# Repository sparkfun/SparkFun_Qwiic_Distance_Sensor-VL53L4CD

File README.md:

SparkFun Distance Sensor - VL53L4CD (Qwiic)
========================================

[*SparkFun Distance Sensor - VL53L4CD (Qwiic) (SEN-18993)*](https://www.sparkfun.com/products/18993)

This SparkFun Distance Sensor Breakout utilizes the VL53L4CD next generation ToF (Time of Flight) sensor module to give you the highly accurate measurements at short ranges for its size. The VL53L4CD from STMicroelectronics uses a VCSEL (Vertical Cavity Surface Emitting Laser) to emit an infrared laser to time the reflection to the target. That means that you will be able to measure the distance to an object from 1mm to 1300mm away with millimeter resolution! To make it even easier to get your readings, all communication is enacted exclusively via I<sup>2</sup>C, utilizing our handy Qwiic system so no soldering is required to connect it to the rest of your system. However, we still have broken out 0.1”-spaced pins in case you prefer to use a breadboard.

Each VL53L4CD sensor features a precision to be 1mm with an accuracy around +/-7mm (white target: 88%, indoor, no infrared) and a minimum read distance of this sensor is 1mm. The field of view for this little breakout has a typical full field of view of 18° with a read rate of up to 100Hz. Make sure to power this board appropriately since it will need 2.6V-3.5V to operate. Lastly, please be sure to remove the protective sticker on the VL53L1X before use otherwise it will, most assuredly, throw off your readings.

**Note:** This is a [CLASS 1](http://en.wikipedia.org/wiki/Laser_safety#Class_1) LASER PRODUCT CLASSIFIED IEC 60825-1 2014.

Repository Contents
-------------------

* **/Hardware** - Eagle design files (.brd, .sch)
* **/Production** - Production panel files (.brd)

Documentation
--------------
* **[Arduino Library](https://github.com/sparkfun/SparkFun_VL53L1X_Arduino_Library)** -  Arduino library for the VL53L1X and VL53L4CD.
* **[VL53L1X Python Package](https://github.com/sparkfun/Qwiic_VL53L1X_Py)** - Python package for the VL53L1X and VL53L4CD.
  * **[ReadtheDocs Documentation](https://qwiic-vl53l1x-py.readthedocs.io/en/latest/)**
* **[Hookup Guide](https://learn.sparkfun.com/tutorials/qwiic-distance-sensor-vl53l1x-vl53l4cd-hookup-guide)** - Basic hookup guide for the VL53L1X and VL53L4CD.

Product Versions
----------------
* [SEN-18993](https://www.sparkfun.com/products/18993) - Initial Release

Version History
---------------
* v1.0 - Initial Release 

License Information
-------------------

This product is _**open source**_! 

Please review the LICENSE.md file for license information. 

If you have any questions or concerns on licensing, please contact technical support on our [SparkFun forums](https://forum.sparkfun.com/viewforum.php?f=152).

Distributed as-is; no warranty is given.

- Your friends at SparkFun.

_<COLLABORATION CREDIT>_

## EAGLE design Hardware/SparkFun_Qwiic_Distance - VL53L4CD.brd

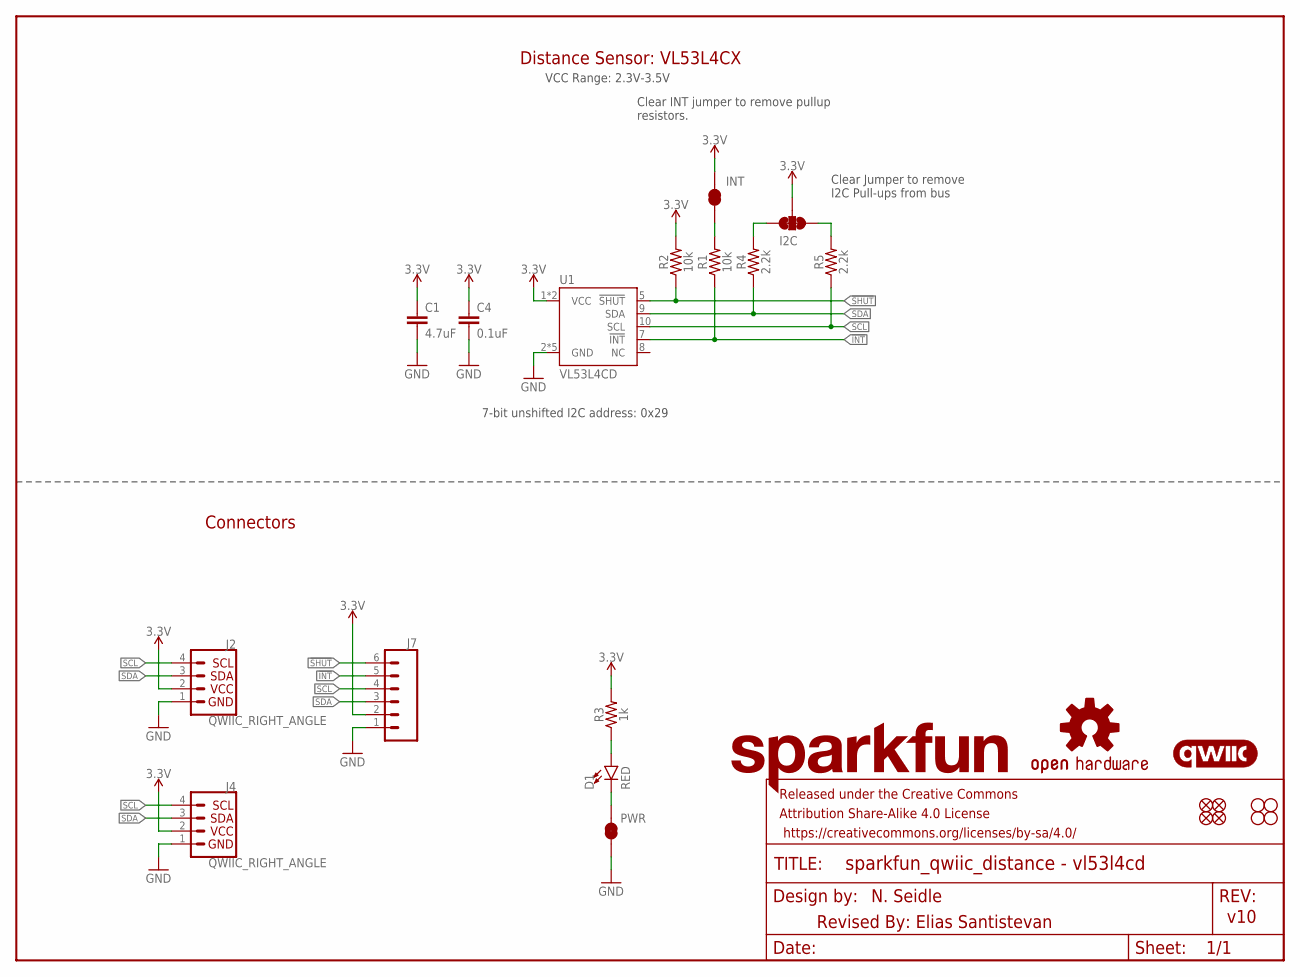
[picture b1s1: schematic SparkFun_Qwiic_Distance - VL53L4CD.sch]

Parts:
C1: 4.7uF; 0603
C4: 0.1uF; 0603
D1: RED; LED-0603
FRAME1: FRAME-LETTER; CREATIVE_COMMONS
I2C: JUMPER-SMT_3_2-NC_TRACE_SILK; SMT-JUMPER_3_2-NC_TRACE_SILK
J2, J4: QWIIC_RIGHT_ANGLE; JST04_1MM_RA
J7: CONN_06NO_SILK_NO_POP; 1X06_NO_SILK
JP1, JP2, JP5, JP6: FIDUCIALUFIDUCIAL; MICRO-FIDUCIAL
JP3, JP4, JP7, JP8: STAND-OFF
JP9: INT; SMT-JUMPER_2_NC_TRACE_SILK
LOGO1: OSHW-LOGOMINI; OSHW-LOGO-MINI
LOGO2: SFE_LOGO_NAME.1_INCH; SFE_LOGO_NAME_.1
LOGO3: QWIIC_LOGO_4MM; QWIIC_4MM
PWR: INT; SMT-JUMPER_2_NC_TRACE_SILK
R1, R2: 10k; 0603
R3: 1k; 0603
R4, R5: 2.2k; 0603
U1: VL53L4CD

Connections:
3.3V: C1.1, C4.1, I2C.2, J2.2, J4.2, J7.2, JP9.2, R2.2, R3.2, U1.1 (VCC), U1.11 (VCC)
!INT: J7.5, R1.1, U1.7 (!INT)
!SHUT: J7.6, R2.1, U1.5 (!SHUT)
GND: C1.2, C4.2, J2.1, J4.1, J7.1, PWR.1, U1.2 (GND), U1.3 (GND), U1.4 (GND), U1.6 (GND), U1.12 (GND)
unnamed: I2C.1, R5.2
unnamed: I2C.3, R4.2
unnamed: D1.A, R3.1
unnamed: JP9.1, R1.2
unnamed: D1.C, PWR.2
SCL: J2.4, J4.4, J7.4, R5.1, U1.10 (SCL)
SDA: J2.3, J4.3, J7.3, R4.1, U1.9 (SDA)

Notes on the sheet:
N. Seidle
v10
7-bit unshifted I2C address: 0x29
Clear Jumper to remove I2C Pull-ups from bus
Clear INT jumper to remove pullup resistors.
Connectors
Distance Sensor: VL53L4CX
VCC Range: 2.3V-3.5V
Revised By: Elias Santistevan

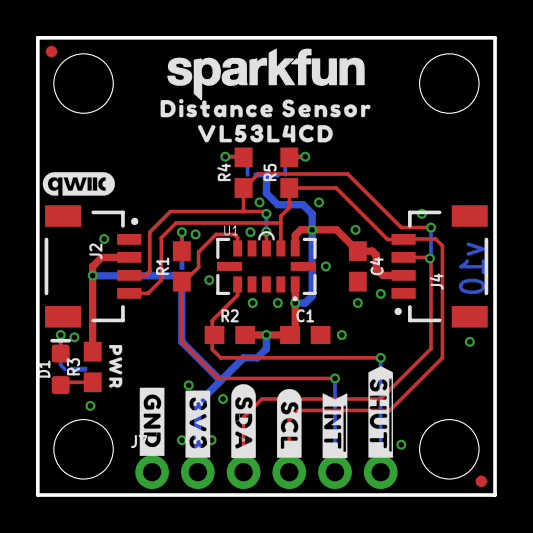
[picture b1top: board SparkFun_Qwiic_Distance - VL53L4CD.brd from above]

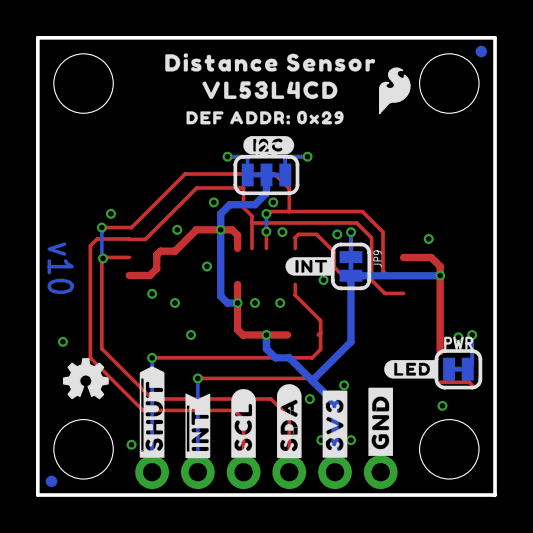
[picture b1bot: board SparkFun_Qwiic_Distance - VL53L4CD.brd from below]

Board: 2 copper layers, 25.4 x 25.4 mm, 50 parts (20 on the bottom side), 11 nets.

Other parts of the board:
U$1, U$12: ##INT##7
U$2, U$13: ##SHUT##6
U$3, U$14: #3V3#1
U$4, U$15: #GND#0
U$5: #I2C#56
U$6, U$16: #SCL#4
U$7, U$17: #SDA#5
U$8, U$18: DISTANCE_SENSOR8
U$9, U$24: VL53L4CD0
U$10: #LED#54
U$11: #INT#55
U$20: DEF_ADDR#54
U$21: 0X2955
U$22: SFE_LOGO_FLAME_.1
U$23: PWR55

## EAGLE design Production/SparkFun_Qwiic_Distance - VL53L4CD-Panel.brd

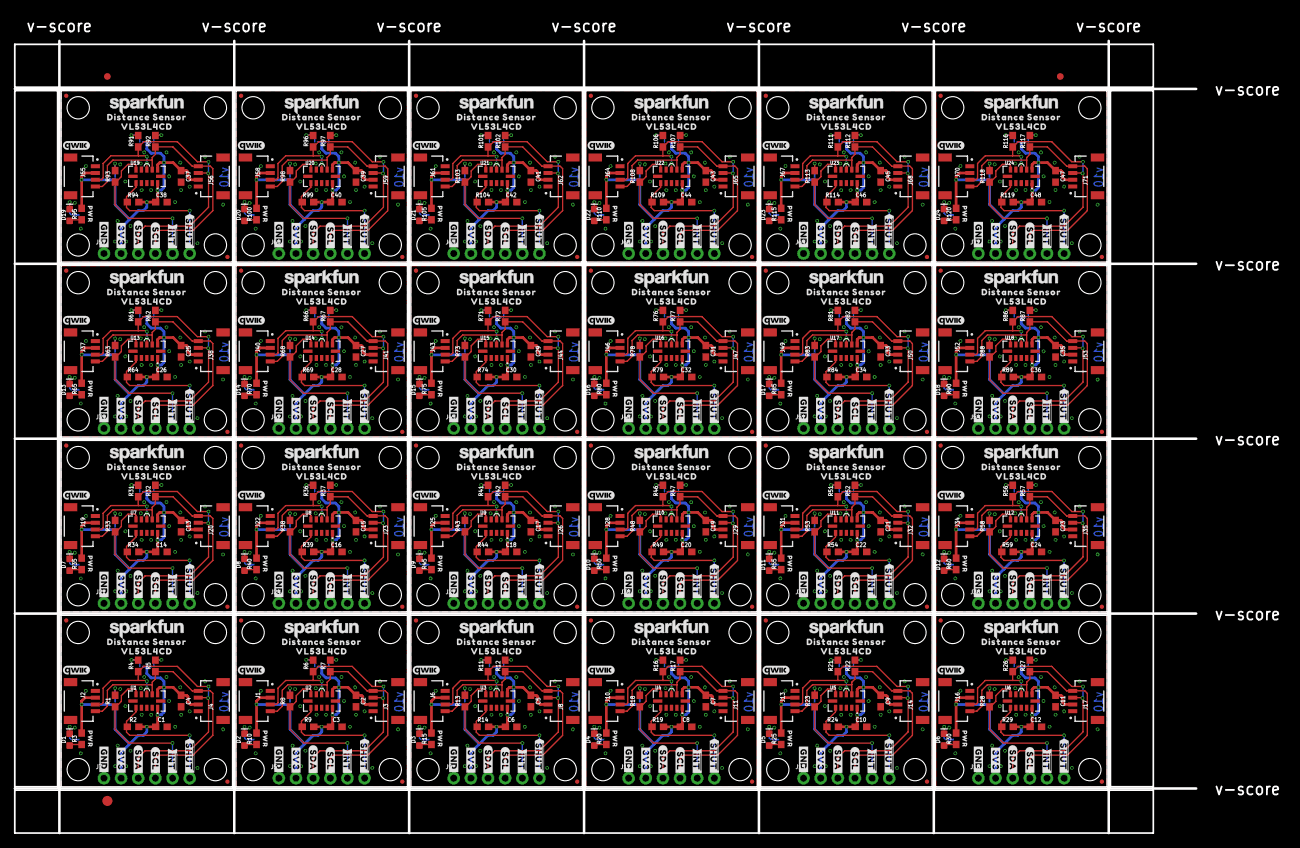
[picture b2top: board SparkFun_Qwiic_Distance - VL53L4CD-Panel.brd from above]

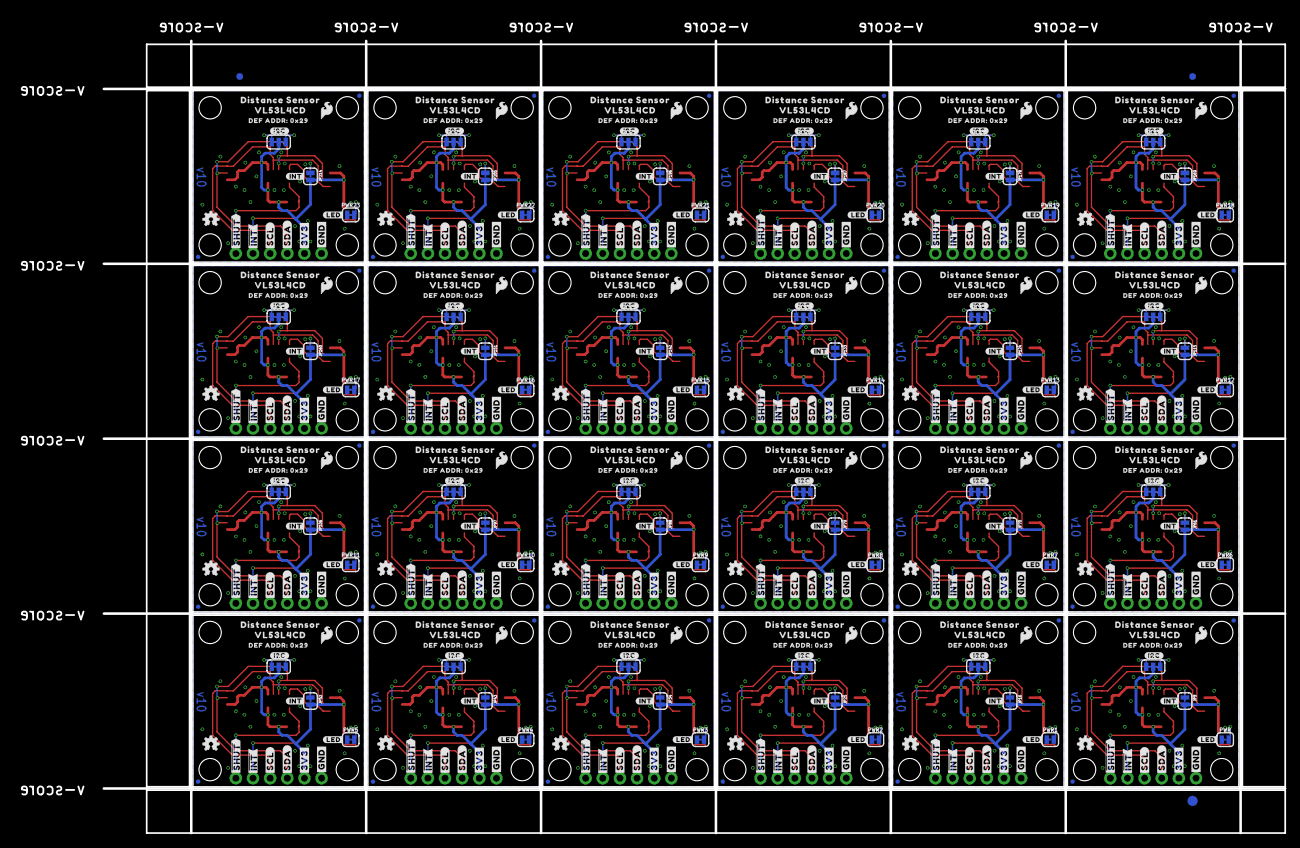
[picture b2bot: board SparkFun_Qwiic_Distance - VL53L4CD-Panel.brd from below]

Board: 2 copper layers, 188.2 x 121.2 mm, 1182 parts (483 on the bottom side), 264 nets.

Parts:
C1, C3, C6, C8, C10, C12, C14, C16, C18, C20, C22, C24, C26, C28, C30, C32, C34, C36, C38, C40, C42, C44, C46, C48: 4.7uF; 0603
C2, C4, C5, C7, C9, C11, C13, C15, C17, C19, C21, C23, C25, C27, C29, C31, C33, C35, C37, C39, C41, C43, C45, C47: 0.1uF; 0603
D1, D2, D3, D4, D5, D6, D7, D8, D9, D10, D11, D12, D13, D14, D15, D16, D17, D18, D19, D20, D21, D22, D23, D24: RED; LED-0603
E$1, E$2, E$3, E$4: FIDUCIAL-1X2
E$5, E$6: FIDUCIAL-1.5X3
I2C, I2C1, I2C2, I2C3, I2C4, I2C5, I2C6, I2C7, I2C8, I2C9, I2C10, I2C11, I2C12, I2C13, I2C14, I2C15, I2C16, I2C17, I2C18, I2C19, I2C20, I2C21, I2C22, I2C23: JUMPER-SMT_3_2-NC_TRACE_SILK; SMT-JUMPER_3_2-NC_TRACE_SILK
J1, J2, J3, J4, J6, J8, J10, J11, J13, J14, J16, J17, J19, J20, J22, J23, J25, J26, J28, J29, J31, J32, J34, J35, J37, J38, J40, J41, J43, J44, J46, J47, J49, J50, J52, J53, J55, J56, J58, J59, J61, J62, J64, J65, J67, J68, J70, J71: QWIIC_RIGHT_ANGLE; JST04_1MM_RA
J5, J7, J9, J12, J15, J18, J21, J24, J27, J30, J33, J36, J39, J42, J45, J48, J51, J54, J57, J60, J63, J66, J69, J72: 1X06_NO_SILK
JP1, JP2, JP5, JP6, JP12, JP13, JP14, JP15, JP21, JP22, JP23, JP24, JP30, JP31, JP32, JP33, JP39, JP40, JP41, JP42, JP48, JP49, JP50, JP51, JP57, JP58, JP59, JP60, JP66, JP67, JP68, JP69, JP75, JP76, JP77, JP78, JP84, JP85, JP86, JP87, JP93, JP94, JP95, JP96, JP102, JP103, JP104, JP105, JP111, JP112, JP113, JP114, JP120, JP121, JP122, JP123, JP129, JP130, JP131, JP132, JP138, JP139, JP140, JP141, JP147, JP148, JP149, JP150, JP156, JP157, JP158, JP159, JP165, JP166, JP167, JP168, JP174, JP175, JP176, JP177, JP183, JP184, JP185, JP186, JP192, JP193, JP194, JP195, JP201, JP202, JP203, JP204, JP210, JP211, JP212, JP213: FIDUCIALUFIDUCIAL; MICRO-FIDUCIAL
JP3, JP4, JP7, JP8, JP10, JP11, JP17, JP18, JP19, JP20, JP26, JP27, JP28, JP29, JP35, JP36, JP37, JP38, JP44, JP45, JP46, JP47, JP53, JP54, JP55, JP56, JP62, JP63, JP64, JP65, JP71, JP72, JP73, JP74, JP80, JP81, JP82, JP83, JP89, JP90, JP91, JP92, JP98, JP99, JP100, JP101, JP107, JP108, JP109, JP110, JP116, JP117, JP118, JP119, JP125, JP126, JP127, JP128, JP134, JP135, JP136, JP137, JP143, JP144, JP145, JP146, JP152, JP153, JP154, JP155, JP161, JP162, JP163, JP164, JP170, JP171, JP172, JP173, JP179, JP180, JP181, JP182, JP188, JP189, JP190, JP191, JP197, JP198, JP199, JP200, JP206, JP207, JP208, JP209, JP215, JP216: STAND-OFF
JP9, JP16, JP25, JP34, JP43, JP52, JP61, JP70, JP79, JP88, JP97, JP106, JP115, JP124, JP133, JP142, JP151, JP160, JP169, JP178, JP187, JP196, JP205, JP214: INT; SMT-JUMPER_2_NC_TRACE_SILK
LOGO1, LOGO4, LOGO7, LOGO10, LOGO13, LOGO16, LOGO19, LOGO22, LOGO25, LOGO28, LOGO31, LOGO34, LOGO37, LOGO40, LOGO43, LOGO46, LOGO49, LOGO52, LOGO55, LOGO58, LOGO61, LOGO64, LOGO67, LOGO70: OSHW-LOGOMINI; OSHW-LOGO-MINI
LOGO2, LOGO5, LOGO8, LOGO11, LOGO14, LOGO17, LOGO20, LOGO23, LOGO26, LOGO29, LOGO32, LOGO35, LOGO38, LOGO41, LOGO44, LOGO47, LOGO50, LOGO53, LOGO56, LOGO59, LOGO62, LOGO65, LOGO68, LOGO71: SFE_LOGO_NAME.1_INCH; SFE_LOGO_NAME_.1
LOGO3, LOGO6, LOGO9, LOGO12, LOGO15, LOGO18, LOGO21, LOGO24, LOGO27, LOGO30, LOGO33, LOGO36, LOGO39, LOGO42, LOGO45, LOGO48, LOGO51, LOGO54, LOGO57, LOGO60, LOGO63, LOGO66, LOGO69, LOGO72: QWIIC_LOGO_4MM; QWIIC_4MM
PWR, PWR1, PWR2, PWR3, PWR4, PWR5, PWR6, PWR7, PWR8, PWR9, PWR10, PWR11, PWR12, PWR13, PWR14, PWR15, PWR16, PWR17, PWR18, PWR19, PWR20, PWR21, PWR22, PWR23: INT; SMT-JUMPER_2_NC_TRACE_SILK
R1, R2, R8, R9, R13, R14, R18, R19, R23, R24, R28, R29, R33, R34, R38, R39, R43, R44, R48, R49, R53, R54, R58, R59, R63, R64, R68, R69, R73, R74, R78, R79, R83, R84, R88, R89, R93, R94, R98, R99, R103, R104, R108, R109, R113, R114, R118, R119: 10k; 0603
R3, R10, R15, R20, R25, R30, R35, R40, R45, R50, R55, R60, R65, R70, R75, R80, R85, R90, R95, R100, R105, R110, R115, R120: 1k; 0603
R4, R5, R6, R7, R11, R12, R16, R17, R21, R22, R26, R27, R31, R32, R36, R37, R41, R42, R46, R47, R51, R52, R56, R57, R61, R62, R66, R67, R71, R72, R76, R77, R81, R82, R86, R87, R91, R92, R96, R97, R101, R102, R106, R107, R111, R112, R116, R117: 2.2k; 0603
U1, U2, U3, U4, U5, U6, U7, U8, U9, U10, U11, U12, U13, U14, U15, U16, U17, U18, U19, U20, U21, U22, U23, U24: VL53L4CX
U$1, U$12, U$19, U$34, U$47, U$57, U$70, U$80, U$93, U$103, U$116, U$126, U$139, U$149, U$162, U$172, U$185, U$195, U$208, U$218, U$231, U$241, U$254, U$264, U$277, U$287, U$300, U$310, U$323, U$333, U$346, U$356, U$369, U$379, U$392, U$402, U$415, U$425, U$438, U$448, U$461, U$471, U$484, U$494, U$507, U$517, U$530, U$540: ##INT##7
U$2, U$13, U$25, U$35, U$48, U$58, U$71, U$81, U$94, U$104, U$117, U$127, U$140, U$150, U$163, U$173, U$186, U$196, U$209, U$219, U$232, U$242, U$255, U$265, U$278, U$288, U$301, U$311, U$324, U$334, U$347, U$357, U$370, U$380, U$393, U$403, U$416, U$426, U$439, U$449, U$462, U$472, U$485, U$495, U$508, U$518, U$531, U$541: ##SHUT##6
U$3, U$14, U$26, U$36, U$49, U$59, U$72, U$82, U$95, U$105, U$118, U$128, U$141, U$151, U$164, U$174, U$187, U$197, U$210, U$220, U$233, U$243, U$256, U$266, U$279, U$289, U$302, U$312, U$325, U$335, U$348, U$358, U$371, U$381, U$394, U$404, U$417, U$427, U$440, U$450, U$463, U$473, U$486, U$496, U$509, U$519, U$532, U$542: #3V3#1
U$4, U$15, U$27, U$37, U$50, U$60, U$73, U$83, U$96, U$106, U$119, U$129, U$142, U$152, U$165, U$175, U$188, U$198, U$211, U$221, U$234, U$244, U$257, U$267, U$280, U$290, U$303, U$313, U$326, U$336, U$349, U$359, U$372, U$382, U$395, U$405, U$418, U$428, U$441, U$451, U$464, U$474, U$487, U$497, U$510, U$520, U$533, U$543: #GND#0
U$5, U$28, U$51, U$74, U$97, U$120, U$143, U$166, U$189, U$212, U$235, U$258, U$281, U$304, U$327, U$350, U$373, U$396, U$419, U$442, U$465, U$488, U$511, U$534: #I2C#56
U$6, U$16, U$29, U$38, U$52, U$61, U$75, U$84, U$98, U$107, U$121, U$130, U$144, U$153, U$167, U$176, U$190, U$199, U$213, U$222, U$236, U$245, U$259, U$268, U$282, U$291, U$305, U$314, U$328, U$337, U$351, U$360, U$374, U$383, U$397, U$406, U$420, U$429, U$443, U$452, U$466, U$475, U$489, U$498, U$512, U$521, U$535, U$544: #SCL#4
U$7, U$17, U$30, U$39, U$53, U$62, U$76, U$85, U$99, U$108, U$122, U$131, U$145, U$154, U$168, U$177, U$191, U$200, U$214, U$223, U$237, U$246, U$260, U$269, U$283, U$292, U$306, U$315, U$329, U$338, U$352, U$361, U$375, U$384, U$398, U$407, U$421, U$430, U$444, U$453, U$467, U$476, U$490, U$499, U$513, U$522, U$536, U$545: #SDA#5
U$8, U$18, U$31, U$40, U$54, U$63, U$77, U$86, U$100, U$109, U$123, U$132, U$146, U$155, U$169, U$178, U$192, U$201, U$215, U$224, U$238, U$247, U$261, U$270, U$284, U$293, U$307, U$316, U$330, U$339, U$353, U$362, U$376, U$385, U$399, U$408, U$422, U$431, U$445, U$454, U$468, U$477, U$491, U$500, U$514, U$523, U$537, U$546: DISTANCE_SENSOR8
U$9, U$24, U$45, U$46, U$68, U$69, U$91, U$92, U$114, U$115, U$137, U$138, U$160, U$161, U$183, U$184, U$206, U$207, U$229, U$230, U$252, U$253, U$275, U$276, U$298, U$299, U$321, U$322, U$344, U$345, U$367, U$368, U$390, U$391, U$413, U$414, U$436, U$437, U$459, U$460, U$482, U$483, U$505, U$506, U$528, U$529, U$551, U$552: VL53L4CD0
U$10, U$32, U$55, U$78, U$101, U$124, U$147, U$170, U$193, U$216, U$239, U$262, U$285, U$308, U$331, U$354, U$377, U$400, U$423, U$446, U$469, U$492, U$515, U$538: #LED#54
U$11, U$33, U$56, U$79, U$102, U$125, U$148, U$171, U$194, U$217, U$240, U$263, U$286, U$309, U$332, U$355, U$378, U$401, U$424, U$447, U$470, U$493, U$516, U$539: #INT#55
U$20, U$41, U$64, U$87, U$110, U$133, U$156, U$179, U$202, U$225, U$248, U$271, U$294, U$317, U$340, U$363, U$386, U$409, U$432, U$455, U$478, U$501, U$524, U$547: DEF_ADDR#54
U$21, U$42, U$65, U$88, U$111, U$134, U$157, U$180, U$203, U$226, U$249, U$272, U$295, U$318, U$341, U$364, U$387, U$410, U$433, U$456, U$479, U$502, U$525, U$548: 0X2955
U$22, U$43, U$66, U$89, U$112, U$135, U$158, U$181, U$204, U$227, U$250, U$273, U$296, U$319, U$342, U$365, U$388, U$411, U$434, U$457, U$480, U$503, U$526, U$549: SFE_LOGO_FLAME_.1
U$23, U$44, U$67, U$90, U$113, U$136, U$159, U$182, U$205, U$228, U$251, U$274, U$297, U$320, U$343, U$366, U$389, U$412, U$435, U$458, U$481, U$504, U$527, U$550: PWR55

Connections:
3.3V: C1.1, C4.1, I2C.2, J2.2, J4.2, J7.2, JP9.2, R2.2, R3.2, U1.1, U1.11
3.3V1: C2.1, C3.1, I2C1.2, J1.2, J3.2, J5.2, JP16.2, R9.2, R10.2, U2.1, U2.11
3.3V2: C5.1, C6.1, I2C2.2, J6.2, J8.2, J9.2, JP25.2, R14.2, R15.2, U3.1, U3.11
3.3V3: C7.1, C8.1, I2C3.2, J10.2, J11.2, J12.2, JP34.2, R19.2, R20.2, U4.1, U4.11
3.3V4: C9.1, C10.1, I2C4.2, J13.2, J14.2, J15.2, JP43.2, R24.2, R25.2, U5.1, U5.11
3.3V5: C11.1, C12.1, I2C5.2, J16.2, J17.2, J18.2, JP52.2, R29.2, R30.2, U6.1, U6.11
3.3V6: C13.1, C14.1, I2C6.2, J19.2, J20.2, J21.2, JP61.2, R34.2, R35.2, U7.1, U7.11
3.3V7: C15.1, C16.1, I2C7.2, J22.2, J23.2, J24.2, JP70.2, R39.2, R40.2, U8.1, U8.11
3.3V8: C17.1, C18.1, I2C8.2, J25.2, J26.2, J27.2, JP79.2, R44.2, R45.2, U9.1, U9.11
3.3V9: C19.1, C20.1, I2C9.2, J28.2, J29.2, J30.2, JP88.2, R49.2, R50.2, U10.1, U10.11
3.3V10: C21.1, C22.1, I2C10.2, J31.2, J32.2, J33.2, JP97.2, R54.2, R55.2, U11.1, U11.11
3.3V11: C23.1, C24.1, I2C11.2, J34.2, J35.2, J36.2, JP106.2, R59.2, R60.2, U12.1, U12.11
3.3V12: C25.1, C26.1, I2C12.2, J37.2, J38.2, J39.2, JP115.2, R64.2, R65.2, U13.1, U13.11
3.3V13: C27.1, C28.1, I2C13.2, J40.2, J41.2, J42.2, JP124.2, R69.2, R70.2, U14.1, U14.11
3.3V14: C29.1, C30.1, I2C14.2, J43.2, J44.2, J45.2, JP133.2, R74.2, R75.2, U15.1, U15.11
3.3V15: C31.1, C32.1, I2C15.2, J46.2, J47.2, J48.2, JP142.2, R79.2, R80.2, U16.1, U16.11
3.3V16: C33.1, C34.1, I2C16.2, J49.2, J50.2, J51.2, JP151.2, R84.2, R85.2, U17.1, U17.11
3.3V17: C35.1, C36.1, I2C17.2, J52.2, J53.2, J54.2, JP160.2, R89.2, R90.2, U18.1, U18.11
3.3V18: C37.1, C38.1, I2C18.2, J55.2, J56.2, J57.2, JP169.2, R94.2, R95.2, U19.1, U19.11
3.3V19: C39.1, C40.1, I2C19.2, J58.2, J59.2, J60.2, JP178.2, R99.2, R100.2, U20.1, U20.11
3.3V20: C41.1, C42.1, I2C20.2, J61.2, J62.2, J63.2, JP187.2, R104.2, R105.2, U21.1, U21.11
3.3V21: C43.1, C44.1, I2C21.2, J64.2, J65.2, J66.2, JP196.2, R109.2, R110.2, U22.1, U22.11
3.3V22: C45.1, C46.1, I2C22.2, J67.2, J68.2, J69.2, JP205.2, R114.2, R115.2, U23.1, U23.11
3.3V23: C47.1, C48.1, I2C23.2, J70.2, J71.2, J72.2, JP214.2, R119.2, R120.2, U24.1, U24.11
!INT: J7.5, R1.1, U1.7
!INT1: J5.5, R8.1, U2.7
!INT2: J9.5, R13.1, U3.7
!INT3: J12.5, R18.1, U4.7
!INT4: J15.5, R23.1, U5.7
!INT5: J18.5, R28.1, U6.7
!INT6: J21.5, R33.1, U7.7
!INT7: J24.5, R38.1, U8.7
!INT8: J27.5, R43.1, U9.7
!INT9: J30.5, R48.1, U10.7
!INT10: J33.5, R53.1, U11.7
!INT11: J36.5, R58.1, U12.7
!INT12: J39.5, R63.1, U13.7
!INT13: J42.5, R68.1, U14.7
!INT14: J45.5, R73.1, U15.7
!INT15: J48.5, R78.1, U16.7
!INT16: J51.5, R83.1, U17.7
!INT17: J54.5, R88.1, U18.7
!INT18: J57.5, R93.1, U19.7
!INT19: J60.5, R98.1, U20.7
!INT20: J63.5, R103.1, U21.7
!INT21: J66.5, R108.1, U22.7
!INT22: J69.5, R113.1, U23.7
!INT23: J72.5, R118.1, U24.7
!SHUT: J7.6, R2.1, U1.5
!SHUT1: J5.6, R9.1, U2.5
!SHUT2: J9.6, R14.1, U3.5
!SHUT3: J12.6, R19.1, U4.5
!SHUT4: J15.6, R24.1, U5.5
!SHUT5: J18.6, R29.1, U6.5
!SHUT6: J21.6, R34.1, U7.5
!SHUT7: J24.6, R39.1, U8.5
!SHUT8: J27.6, R44.1, U9.5
!SHUT9: J30.6, R49.1, U10.5
!SHUT10: J33.6, R54.1, U11.5
!SHUT11: J36.6, R59.1, U12.5
!SHUT12: J39.6, R64.1, U13.5
!SHUT13: J42.6, R69.1, U14.5
!SHUT14: J45.6, R74.1, U15.5
!SHUT15: J48.6, R79.1, U16.5
!SHUT16: J51.6, R84.1, U17.5
!SHUT17: J54.6, R89.1, U18.5
!SHUT18: J57.6, R94.1, U19.5
!SHUT19: J60.6, R99.1, U20.5
!SHUT20: J63.6, R104.1, U21.5
!SHUT21: J66.6, R109.1, U22.5
!SHUT22: J69.6, R114.1, U23.5
!SHUT23: J72.6, R119.1, U24.5
GND: C1.2, C4.2, J2.1, J4.1, J7.1, PWR.1, U1.2, U1.3, U1.4, U1.6, U1.12
GND1: C2.2, C3.2, J1.1, J3.1, J5.1, PWR1.1, U2.2, U2.3, U2.4, U2.6, U2.12
GND2: C5.2, C6.2, J6.1, J8.1, J9.1, PWR2.1, U3.2, U3.3, U3.4, U3.6, U3.12
GND3: C7.2, C8.2, J10.1, J11.1, J12.1, PWR3.1, U4.2, U4.3, U4.4, U4.6, U4.12
GND4: C9.2, C10.2, J13.1, J14.1, J15.1, PWR4.1, U5.2, U5.3, U5.4, U5.6, U5.12
GND5: C11.2, C12.2, J16.1, J17.1, J18.1, PWR5.1, U6.2, U6.3, U6.4, U6.6, U6.12
GND6: C13.2, C14.2, J19.1, J20.1, J21.1, PWR6.1, U7.2, U7.3, U7.4, U7.6, U7.12
GND7: C15.2, C16.2, J22.1, J23.1, J24.1, PWR7.1, U8.2, U8.3, U8.4, U8.6, U8.12
GND8: C17.2, C18.2, J25.1, J26.1, J27.1, PWR8.1, U9.2, U9.3, U9.4, U9.6, U9.12
GND9: C19.2, C20.2, J28.1, J29.1, J30.1, PWR9.1, U10.2, U10.3, U10.4, U10.6, U10.12
GND10: C21.2, C22.2, J31.1, J32.1, J33.1, PWR10.1, U11.2, U11.3, U11.4, U11.6, U11.12
GND11: C23.2, C24.2, J34.1, J35.1, J36.1, PWR11.1, U12.2, U12.3, U12.4, U12.6, U12.12
GND12: C25.2, C26.2, J37.1, J38.1, J39.1, PWR12.1, U13.2, U13.3, U13.4, U13.6, U13.12
GND13: C27.2, C28.2, J40.1, J41.1, J42.1, PWR13.1, U14.2, U14.3, U14.4, U14.6, U14.12
GND14: C29.2, C30.2, J43.1, J44.1, J45.1, PWR14.1, U15.2, U15.3, U15.4, U15.6, U15.12
GND15: C31.2, C32.2, J46.1, J47.1, J48.1, PWR15.1, U16.2, U16.3, U16.4, U16.6, U16.12
GND16: C33.2, C34.2, J49.1, J50.1, J51.1, PWR16.1, U17.2, U17.3, U17.4, U17.6, U17.12
GND17: C35.2, C36.2, J52.1, J53.1, J54.1, PWR17.1, U18.2, U18.3, U18.4, U18.6, U18.12
GND18: C37.2, C38.2, J55.1, J56.1, J57.1, PWR18.1, U19.2, U19.3, U19.4, U19.6, U19.12
GND19: C39.2, C40.2, J58.1, J59.1, J60.1, PWR19.1, U20.2, U20.3, U20.4, U20.6, U20.12
GND20: C41.2, C42.2, J61.1, J62.1, J63.1, PWR20.1, U21.2, U21.3, U21.4, U21.6, U21.12
GND21: C43.2, C44.2, J64.1, J65.1, J66.1, PWR21.1, U22.2, U22.3, U22.4, U22.6, U22.12
GND22: C45.2, C46.2, J67.1, J68.1, J69.1, PWR22.1, U23.2, U23.3, U23.4, U23.6, U23.12
GND23: C47.2, C48.2, J70.1, J71.1, J72.1, PWR23.1, U24.2, U24.3, U24.4, U24.6, U24.12
unnamed: I2C.1, R5.2
unnamed: I2C.3, R4.2
unnamed: D1.A, R3.1
unnamed: JP9.1, R1.2
unnamed: D1.C, PWR.2
unnamed: I2C1.1, R7.2
unnamed: I2C1.3, R6.2
unnamed: JP16.1, R8.2
unnamed: D2.A, R10.1
unnamed: D2.C, PWR1.2
unnamed: I2C2.1, R12.2
unnamed: I2C2.3, R11.2
unnamed: JP25.1, R13.2
unnamed: D3.A, R15.1
unnamed: D3.C, PWR2.2
unnamed: I2C3.1, R17.2
unnamed: I2C3.3, R16.2
unnamed: JP34.1, R18.2
unnamed: D4.A, R20.1
unnamed: D4.C, PWR3.2
unnamed: I2C4.1, R22.2
unnamed: I2C4.3, R21.2
unnamed: JP43.1, R23.2
unnamed: D5.A, R25.1
unnamed: D5.C, PWR4.2
unnamed: I2C5.1, R27.2
unnamed: I2C5.3, R26.2
unnamed: JP52.1, R28.2
unnamed: D6.A, R30.1
unnamed: D6.C, PWR5.2
unnamed: I2C6.1, R32.2
unnamed: I2C6.3, R31.2
unnamed: JP61.1, R33.2
unnamed: D7.A, R35.1
unnamed: D7.C, PWR6.2
unnamed: I2C7.1, R37.2
unnamed: I2C7.3, R36.2
unnamed: JP70.1, R38.2
unnamed: D8.A, R40.1
unnamed: D8.C, PWR7.2
unnamed: I2C8.1, R42.2
unnamed: I2C8.3, R41.2
unnamed: JP79.1, R43.2
unnamed: D9.A, R45.1
unnamed: D9.C, PWR8.2
unnamed: I2C9.1, R47.2
unnamed: I2C9.3, R46.2
unnamed: JP88.1, R48.2
unnamed: D10.A, R50.1
unnamed: D10.C, PWR9.2
unnamed: I2C10.1, R52.2
unnamed: I2C10.3, R51.2
unnamed: JP97.1, R53.2
unnamed: D11.A, R55.1
unnamed: D11.C, PWR10.2
unnamed: I2C11.1, R57.2
unnamed: I2C11.3, R56.2
unnamed: JP106.1, R58.2
unnamed: D12.A, R60.1
unnamed: D12.C, PWR11.2
unnamed: I2C12.1, R62.2
unnamed: I2C12.3, R61.2
unnamed: JP115.1, R63.2
unnamed: D13.A, R65.1
unnamed: D13.C, PWR12.2
unnamed: I2C13.1, R67.2
unnamed: I2C13.3, R66.2
unnamed: JP124.1, R68.2
unnamed: D14.A, R70.1
unnamed: D14.C, PWR13.2
unnamed: I2C14.1, R72.2
unnamed: I2C14.3, R71.2
unnamed: JP133.1, R73.2
unnamed: D15.A, R75.1
unnamed: D15.C, PWR14.2
unnamed: I2C15.1, R77.2
unnamed: I2C15.3, R76.2
unnamed: JP142.1, R78.2
unnamed: D16.A, R80.1
unnamed: D16.C, PWR15.2
unnamed: I2C16.1, R82.2
unnamed: I2C16.3, R81.2
unnamed: JP151.1, R83.2
unnamed: D17.A, R85.1
unnamed: D17.C, PWR16.2
unnamed: I2C17.1, R87.2
unnamed: I2C17.3, R86.2
unnamed: JP160.1, R88.2
unnamed: D18.A, R90.1
unnamed: D18.C, PWR17.2
unnamed: I2C18.1, R92.2
unnamed: I2C18.3, R91.2
unnamed: JP169.1, R93.2
unnamed: D19.A, R95.1
unnamed: D19.C, PWR18.2
unnamed: I2C19.1, R97.2
unnamed: I2C19.3, R96.2
unnamed: JP178.1, R98.2
unnamed: D20.A, R100.1
unnamed: D20.C, PWR19.2
unnamed: I2C20.1, R102.2
unnamed: I2C20.3, R101.2
unnamed: JP187.1, R103.2
unnamed: D21.A, R105.1
unnamed: D21.C, PWR20.2
unnamed: I2C21.1, R107.2
unnamed: I2C21.3, R106.2
unnamed: JP196.1, R108.2
unnamed: D22.A, R110.1
unnamed: D22.C, PWR21.2
unnamed: I2C22.1, R112.2
unnamed: I2C22.3, R111.2
unnamed: JP205.1, R113.2
unnamed: D23.A, R115.1
unnamed: D23.C, PWR22.2
unnamed: I2C23.1, R117.2
unnamed: I2C23.3, R116.2
unnamed: JP214.1, R118.2
unnamed: D24.A, R120.1
unnamed: D24.C, PWR23.2
SCL: J2.4, J4.4, J7.4, R5.1, U1.10
SCL1: J1.4, J3.4, J5.4, R7.1, U2.10
SCL2: J6.4, J8.4, J9.4, R12.1, U3.10
SCL3: J10.4, J11.4, J12.4, R17.1, U4.10
SCL4: J13.4, J14.4, J15.4, R22.1, U5.10
SCL5: J16.4, J17.4, J18.4, R27.1, U6.10
SCL6: J19.4, J20.4, J21.4, R32.1, U7.10
SCL7: J22.4, J23.4, J24.4, R37.1, U8.10
SCL8: J25.4, J26.4, J27.4, R42.1, U9.10
SCL9: J28.4, J29.4, J30.4, R47.1, U10.10
SCL10: J31.4, J32.4, J33.4, R52.1, U11.10
SCL11: J34.4, J35.4, J36.4, R57.1, U12.10
SCL12: J37.4, J38.4, J39.4, R62.1, U13.10
SCL13: J40.4, J41.4, J42.4, R67.1, U14.10
SCL14: J43.4, J44.4, J45.4, R72.1, U15.10
SCL15: J46.4, J47.4, J48.4, R77.1, U16.10
SCL16: J49.4, J50.4, J51.4, R82.1, U17.10
SCL17: J52.4, J53.4, J54.4, R87.1, U18.10
SCL18: J55.4, J56.4, J57.4, R92.1, U19.10
SCL19: J58.4, J59.4, J60.4, R97.1, U20.10
SCL20: J61.4, J62.4, J63.4, R102.1, U21.10
SCL21: J64.4, J65.4, J66.4, R107.1, U22.10
SCL22: J67.4, J68.4, J69.4, R112.1, U23.10
SCL23: J70.4, J71.4, J72.4, R117.1, U24.10
SDA: J2.3, J4.3, J7.3, R4.1, U1.9
SDA1: J1.3, J3.3, J5.3, R6.1, U2.9
SDA2: J6.3, J8.3, J9.3, R11.1, U3.9
SDA3: J10.3, J11.3, J12.3, R16.1, U4.9
SDA4: J13.3, J14.3, J15.3, R21.1, U5.9
SDA5: J16.3, J17.3, J18.3, R26.1, U6.9
SDA6: J19.3, J20.3, J21.3, R31.1, U7.9
SDA7: J22.3, J23.3, J24.3, R36.1, U8.9
SDA8: J25.3, J26.3, J27.3, R41.1, U9.9
SDA9: J28.3, J29.3, J30.3, R46.1, U10.9
SDA10: J31.3, J32.3, J33.3, R51.1, U11.9
SDA11: J34.3, J35.3, J36.3, R56.1, U12.9
SDA12: J37.3, J38.3, J39.3, R61.1, U13.9
SDA13: J40.3, J41.3, J42.3, R66.1, U14.9
SDA14: J43.3, J44.3, J45.3, R71.1, U15.9
SDA15: J46.3, J47.3, J48.3, R76.1, U16.9
SDA16: J49.3, J50.3, J51.3, R81.1, U17.9
SDA17: J52.3, J53.3, J54.3, R86.1, U18.9
SDA18: J55.3, J56.3, J57.3, R91.1, U19.9
SDA19: J58.3, J59.3, J60.3, R96.1, U20.9
SDA20: J61.3, J62.3, J63.3, R101.1, U21.9
SDA21: J64.3, J65.3, J66.3, R106.1, U22.9
SDA22: J67.3, J68.3, J69.3, R111.1, U23.9
SDA23: J70.3, J71.3, J72.3, R116.1, U24.9

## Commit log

2021-11-05 Adds silk to the product
2021-11-05 Replaces INT silk with OUTPUT style flag, adds revised by to attribution in board
    * 3.3V traces bumped to 16mils
    * Moves some silk to keep them from touching
    * Adds PWR silk
    * Adjusts some overlapping part labels
    * Corrects distance sensor name in library
2021-11-10 Adds one via
2021-11-10 Adds Production Files
2021-11-10 Adds PROD_ID to distance sensor
2021-11-16 Corrects part name, and changes eagle file names to reflect the change.
2021-11-16 Adds new panel with corrected name
2021-11-16 Removes old production files
2021-11-16 Updates Distance Sensor Part name

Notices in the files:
parts and their libraries:
SparkFun-Resistors: Licensing: Creative Commons ShareAlike 4.0 International - https://creativecommons.org/licenses/by-sa/4.0
SparkFun-Aesthetics: Released under the Creative Commons Attribution Share-Alike 4.0 License
SparkFun-Aesthetics: https://creativecommons.org/licenses/by-sa/4.0
